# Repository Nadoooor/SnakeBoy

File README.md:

# SnakeBoy
------

------

## Description:
SnakeBoy is a custom snake-themed handheld gaming console powered by the ESP32. Featuring built-in Wi-Fi and Bluetooth connectivity, it supports multiplayer gaming, wireless ROM transfers, and retro emulation for a wide range of classic systems.

## Why Iam making This?
I'm making this Device so i can play soo many games on a handheld device that i can take anywhere. And also as a teen from Gen z, i want to try the games my family was playing before my Gen. Like, Super mario, etc.. (dk any other games' names 👀)

## Highlight:
The Device is fully snake-themed and it has a snake had on the top of the device that looks so cool, I just like snakes so much.

## How it works:
1. Charge the battery if it is not charged.
2. Add all the games on the SD card and plug it from the inside.
3. Switch on the device and wait for it to boot.
4. Open your games and have fun yay.

## Some photos of the project:
### PCB:

### 3D PCB:

### Schematic:

### 3D Case & Assembly:

> [!NOTE]
> Here you are the [Onshape Docs](https://cad.onshape.com/documents/0e87dfd5407f7a465ae1d2e0/w/c71d8217d927d32bb865edde/e/80890fb331397a75dcc65cb7)

### The Project's Zine-Page:

## Bill of Materials (BOM)
|Item Name                                                                                    |Purchase Link                                                                                                                                                                  |Quantity    |Price per Unit|Total  |
|---------------------------------------------------------------------------------------------|-------------------------------------------------------------------------------------------------------------------------------------------------------------------------------|------------|--------------|-------|
|TFT LCD Display Module SPI Interface 1.8 Inch 128*160?(the biggest available and cheap)      |[Here](https://makerselectronics.com/product/tft-lcd-display-module-spi-interface-1-8-inch-128160/)                                                                            |1           |$5            |$5     |
|12*12mm buttons would be great for the (X Y B A)                                             |[Here](https://makerselectronics.com/product/omron-tact-button-switch-12x12x7-3mm/)                                                                                            |4           |$0.07         |$0.28  |
|6*6 mm buttons would be enough for the (Start & Select)                                      |[Here](https://makerselectronics.com/product/mini-push-button-switch-2-pin-6x6x5/)                                                                                             |2           |$0.02         |$0.04  |
|2-Axis joystick for the motion would be super greaat!! (Will recycle it from an old Joystick)|[Here](https://amzn.eu/d/062qHba5)                                                                                                                                             |2 (one pack)|$5            |$5     |
|MAX98357 I2S Sound module                                                                    |[Here](https://makerselectronics.com/product/max98357a-i2s-amplifier-module/?srsltid=AfmBOoqHs1ns5uzBYg7fnzx3AUjoPjrolkP2ksKwE4xoCB8UP14oYwH7)                                 |1           |$2.42         |$2.42  |
|Speaker 8? 0.25W (  29mm)                                                                    |[Here](https://makerselectronics.com/product/speaker-8%CF%89-0-25w-o-29mm/?srsltid=AfmBOorb6pDF3PQixNvZZQCcwQdY1Ptj7M1GuJB8EQ9YuY6uzV3vKMNH)                                   |2           |$0.20         |$0.40  |
|4000mAh 3.7V Lipo Battery                                                                    |[Here](https://www.ram-e-shop.com/shop/bt-854985p-4000mah-polymer-li-ion-3-7v-4000mah-single-cell-battery-6795)                                                                |1           |$7.57         |$7.57  |
|BMS 1S TP4056 (5V -1A) ( Type C ) With Protection                                            |[Here](https://mostelectronic.com/shop/batteries-accessories/battery-accessories/bms-1s-tp4056-5v-1a-lithium-battery-charger-board-type-c-with-protection/)                    |1           |$0.30         |$0.30  |
|Slide Switch Right-Angle SPDT 3 Pin SK12D02VG7                                               |[Here](https://mostelectronic.com/shop/components/switches/slide-switch-right-angle-spdt-3pin-sk12d02vg7/)                                                                     |1           |$0.08         |$0.08  |
|PCB (From JLCPCB)                                                                            |[Here](https://jlcpcb.com)                                                                                                                                                     |5           |$2.00         |$10    |
|PCB (From JLCPCB) SHIPPING                                                                   |[Here](https://jlcpcb.com)                                                                                                                                                     |1           |$20           |$20    |
|3D printing (Local Printing Service)                                                         |[Here](https://printfy3d.myeasyorders.com/pages/print-on-demand)                                                                                                               |3           |~~            |$60    |
|M3 screws (Lengths are in the Onshape Docs)                                                  |[Here](https://uge-one.com/product/m3x10-stainless-steel-304-thread-m3-10-hexagon-head-screws-allen-round-head-screw/?srsltid=AfmBOortaviQvLqRLEaLlDNrt_PPweC_W_sIUYLSHxxqcUGZ4l5zKlip)|2           |$0.10         |$0.10  |
|S2B-XH-A-1 JST XH Data Terminal Angle Male 2 Pin Connector Header 2.5mm                      |[Here](https://makerselectronics.com/product/s2b-xh-a-1-jst-xh-2-pin-header-2-5mm/)                                                                                            |3           |$0.02         |$0.06  |
|Female Pin-headers                                                                           |[Here](https://makerselectronics.com/product/osepp-female-headers/)                                                                                                            |10(one pack)|$4.70         |$4.70  |
|ESP32-S3-N16R8 Development Board WIFI and Bluetooth                                          |[Here](https://mostelectronic.com/shop/arduino-development-boards/esp32-s3-n16r8-development-board-wifi-and-bluetooth/)                                                        |1           |$13.13        |$13.13 |
|Resistor 10k ohm 1/4W                                                                        |[Here](https://mostelectronic.com/shop/components/resistor-10-kohm/)                                                                                                           |7           |$0.03         |$0.03  |
|Total                                                                                        |~~                                                                                                                                                                             |~~          |~~            |$129.11|

## How to Build:
> [!NOTE]
> You can find build guide for the Code [here](https://github.com/Nadoooor/retro-go/blob/ccc14cb922c1a1bcdeadaa2684e8e6cdf3d149d9/BUILDING.md)

1. 3D print and get all the parts.
2. Solder all the components in the PCB.
3. Use the Female Pin-Headers for easy installation for the screen & ESP32 S3.
5. Put the PCB into the case.
4. Plug the speakers and the battery.
6. Double face for the speakers would be enough.
7. close the front Case with the screw.
8. Plug the ESP32 S3 to your laptop and Upload the firmware.
9. Close the back-cover.
10. Switch on the device and ENJOYYY ❤️.

-------
# Made With ❤️, By Nadooor

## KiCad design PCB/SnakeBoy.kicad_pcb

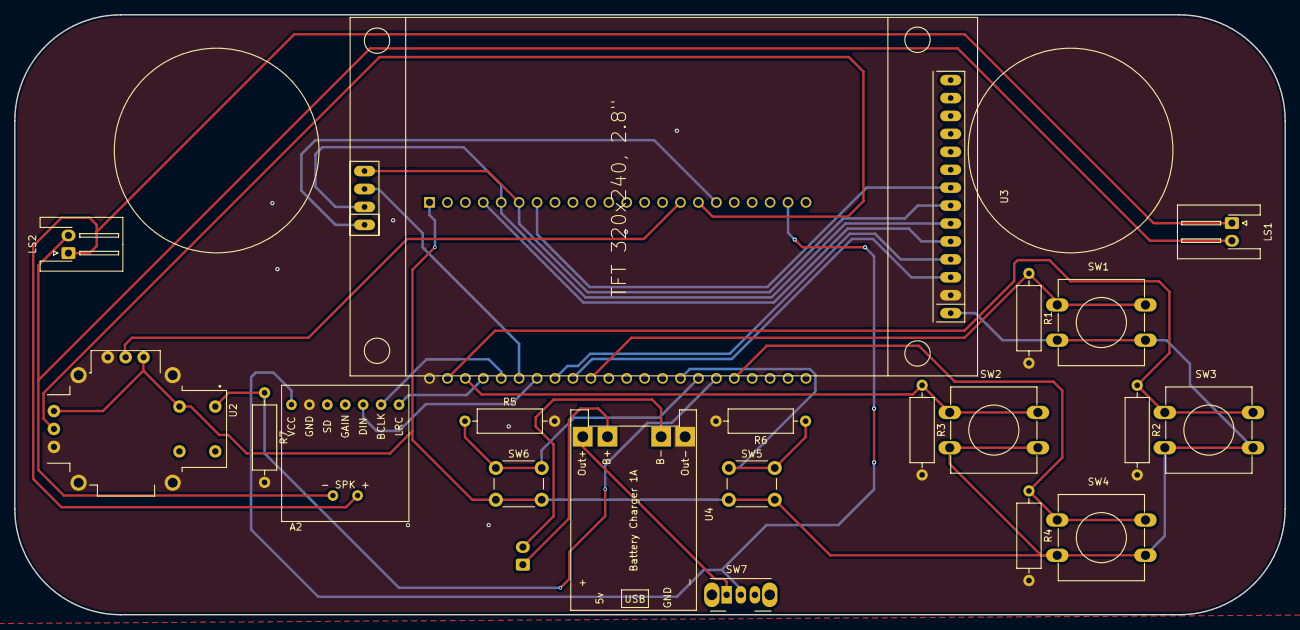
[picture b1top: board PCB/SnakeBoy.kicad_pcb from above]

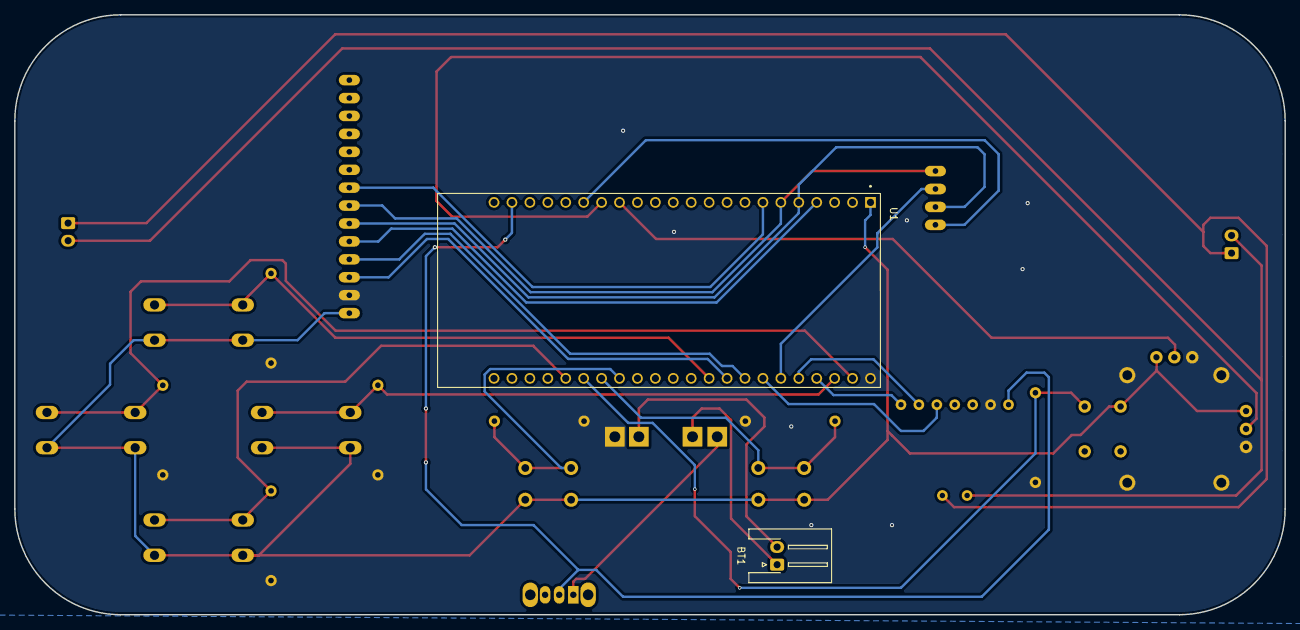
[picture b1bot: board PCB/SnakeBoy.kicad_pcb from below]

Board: 2 copper layers, 180.0 x 85.0 mm, 22 parts (2 on the bottom side), 28 nets.

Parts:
A2: max98357
BT1: Battery; JST_XH_S2B-XH-A-1_1x02_P2.50mm_Horizontal
LS1: Speaker_R; JST_XH_S2B-XH-A-1_1x02_P2.50mm_Horizontal
LS2: Speaker_L; JST_XH_S2B-XH-A-1_1x02_P2.50mm_Horizontal
R1, R2, R3, R4, R5, R6, R7: 10Kohm; R_Axial_DIN0309_L9.0mm_D3.2mm_P12.70mm_Horizontal
SW1: X; SW_PUSH-12mm
SW2: A; SW_PUSH-12mm
SW3: Y; SW_PUSH-12mm
SW4: B; SW_PUSH-12mm
SW5: Start; SW_PUSH_6mm
SW6: Select; SW_PUSH_6mm
SW7: Power_SW; SW_Slide_SPDT_Angled_CK_OS102011MA1Q
U1: ESP32-S3-DEVKITC-1-N16R8; ESP32-S3-DEVKITC-1-N8R8
U2: Joystick; XDCR_COM-09032
U3: TFT_320x240; TFT-320x240
U4: TP4056 Module; TP4056-18650

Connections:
3v3+: SW1.2, SW2.2, SW3.2, SW4.2, SW5.2, SW6.2, U1.J1_1 (3V3), U2.B2A (SEL-), U2.H1 (H+), U2.V1 (V+), U3.1 (VCC)
3v7+: A2.7 (VCC), SW7.2, U1.J1_21 (5V0)
3v7-: A2.6 (GND), R1.2, R2.2, R3.2, R4.2, R5.2, R6.2, R7.2, U1.J3_1 (GND), U2.H3 (H-), U2.S1 (SHIELD), U2.S2 (SHIELD), U2.S3 (SHIELD), U2.S4 (SHIELD), U2.V3 (V-), U3.2 (GND), U4.4 (OUT-)
BCLK: A2.2 (BLCK), U1.J3_5 (GPIO2)
BT_A: R3.1, SW2.1, U1.J3_3 (U0RXD/GPIO44)
BT_B: R4.1, SW4.1, U1.J3_18 (GPIO21)
BT_Select: R5.1, SW6.1, U1.J3_16 (GPIO48)
BT_Start: R6.1, SW5.1, U1.J3_15 (GPIO45)
BT_X: R1.1, SW1.1, U1.J3_10 (GPIO38)
BT_Y: R2.1, SW3.1, U1.J3_2 (U0TXD/GPIO43)
BT_joymid: R7.1, U1.J3_17 (GPIO47), U2.B1A (SEL+)
DIN: A2.3 (DIN), U1.J3_7 (MTDI/GPIO41)
Joy_X: U1.J1_16 (GPIO10), U2.H2 (H)
Joy_Y: U1.J1_15 (GPIO9), U2.V2 (V)
LOut+: A2.9 (SPK+), LS1.2, LS2.2
LOut-: A2.8 (SPK-), LS1.1, LS2.1
LRC: A2.1 (LRC), U1.J3_4 (GPIO1)
unnamed: BT1.1 (+), U4.5 (Batt+)
unnamed: BT1.2 (-), U4.6 (Batt-)
unnamed: SW7.1, U4.3 (OUT+)
SD_CLK: U1.J1_6 (GPIO6), U3.7 (SCK), U3.18 (SD_SCK)
SD_CS: U1.J1_17 (GPIO11), U3.15 (SD_CS)
SD_MISO: U1.J3_6 (MTMS/GPIO42), U3.17 (SD_MISO)
SD_MOSI: U1.J1_5 (GPIO5), U3.6 (MOSI), U3.16 (SD_MOSI)
TFT_BL: U1.J1_7 (GPIO7), U3.8 (LED)
TFT_CS: U1.J3_9 (MTCK/GPIO39), U3.3 (CS)
TFT_DC: U1.J1_4 (GPIO4), U3.5 (DC)
TFT_RST: U1.J3_8 (MTDO/GPIO40), U3.4 (RST)

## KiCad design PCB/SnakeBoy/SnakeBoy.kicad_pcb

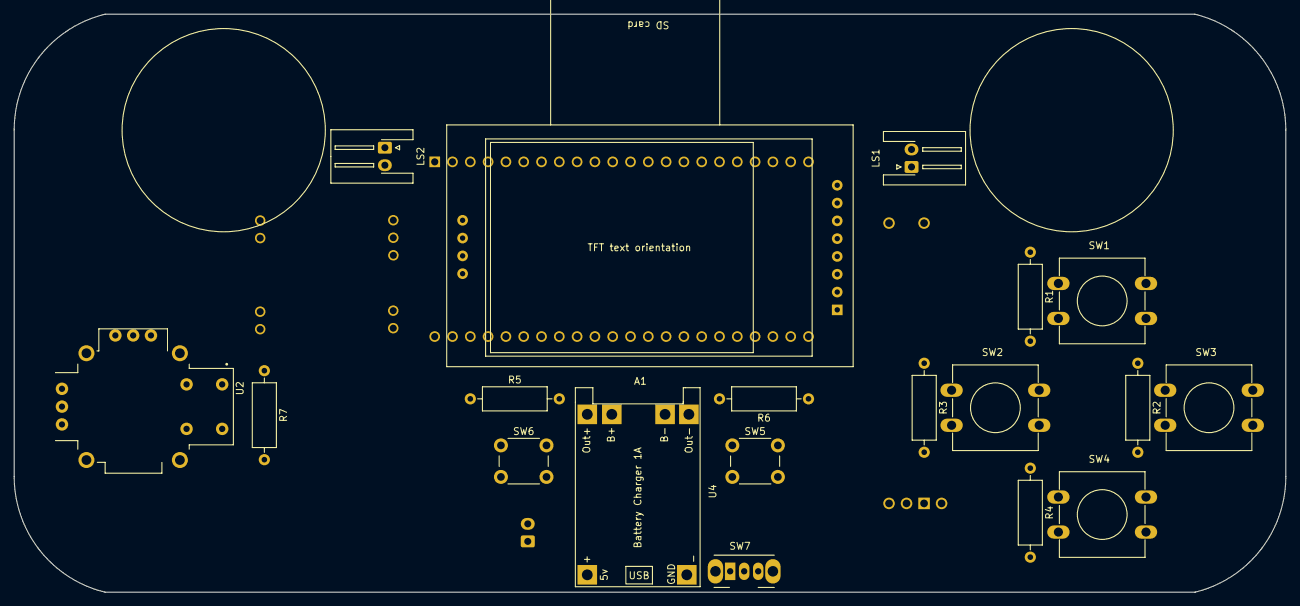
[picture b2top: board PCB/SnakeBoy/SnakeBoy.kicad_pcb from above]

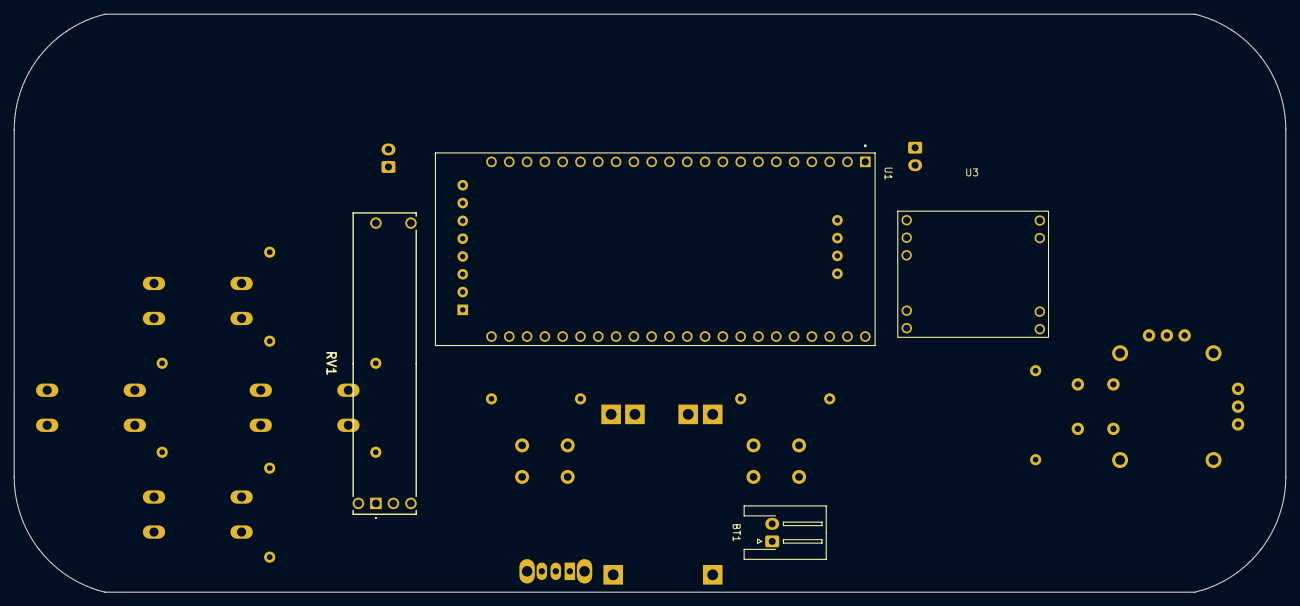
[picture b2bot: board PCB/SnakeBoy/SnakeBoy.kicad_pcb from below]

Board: 2 copper layers, 181.5 x 82.5 mm, 23 parts (4 on the bottom side), 12 nets, no tracks yet.

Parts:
A1: TFT 1.8 inch; Module_TFT_1.8_160x128
BT1: Battery; JST_XH_S2B-XH-A-1_1x02_P2.50mm_Horizontal
LS1, LS2: Speaker; JST_XH_S2B-XH-A-1_1x02_P2.50mm_Horizontal
R1, R2, R3, R4, R5, R6, R7: 10Kohm; R_Axial_DIN0309_L9.0mm_D3.2mm_P12.70mm_Horizontal
RV1: R_Potentiometer_Dual; PS45M0MC2BR10KN
SW1: X; SW_PUSH-12mm
SW2: A; SW_PUSH-12mm
SW3: Y; SW_PUSH-12mm
SW4: B; SW_PUSH-12mm
SW5: Start; SW_PUSH_6mm
SW6: Select; SW_PUSH_6mm
SW7: Power_SW; SW_Slide_SPDT_Angled_CK_OS102011MA1Q
U1: ESP32-S3-DEVKITC-1-N16R8; ESP32-S3-DEVKITC-1-N8R8
U2: Joystick; XDCR_COM-09032
U3: PAM8304 Module; PAM8403
U4: TP4056 Module; TP4056-18650

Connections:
3v7+: A1.6R (VCC), SW1.2, SW2.2, SW3.2, SW4.2, SW5.2, SW7.2, U2.B2A (SEL-), U2.H1 (H+), U2.V1 (V+), U3.1 (5v+)
3v7-: A1.8R (GND), R1.2, R2.2, R3.2, R4.2, R5.2, R6.2, R7.2, U2.H3 (H-), U2.S1 (SHIELD), U2.S2 (SHIELD), U2.S3 (SHIELD), U2.S4 (SHIELD), U2.V3 (V-), U3.2 (GND), U3.4 (GND), U4.4 (OUT-)
BT_A: R3.1, SW2.1
BT_B: R4.1, SW4.1
BT_Select: R5.1, SW6.1
BT_Start: R6.1, SW5.1
BT_X: R1.1, SW1.1
BT_Y: R2.1, SW3.1
BT_joymid: R7.1, U2.B1A (SEL+)
unnamed: BT1.1 (+), U4.5 (Batt+)
unnamed: BT1.2 (-), U4.6 (Batt-)
unnamed: SW7.1, U4.3 (OUT+)

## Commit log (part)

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2026-05-23 Added all the components
2026-05-24 Finished the Controller and Display schems
2026-05-25 Finished the schematic
2026-05-26 Outlined the PCB
2026-05-26 fixing pathes
2026-05-26 fix the gitignore file
2026-05-26 Finished tracing the PCB
2026-06-07 Cloning the firmware source code from "@retroelec"
2026-06-09 Changed the firmware to Retro-Go
2026-06-09 add submodule my retro-go fork
2026-06-10 Edited the PCB to match the firmware
2026-06-11 Adding render photos
2026-06-17 Added the zine
2026-06-26 Wrote the README.md
2026-06-26 Fixeed the zine size in the readme
2026-06-26 Also the first image
2026-06-26 Hyper linked the BOM links
2026-06-26 Tidded up the Directories
2026-06-26 Added the JOURNAL.md
2026-06-26 Revise journal note for clarity and importance
    Updated note to emphasize the importance of project details and logging.
